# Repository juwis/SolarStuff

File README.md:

# SolarStuff on SolarFlight.info
1. brushless esc with integrated MPPT
 * [Software](https://github.com/juwis/SolarStuff/tree/master/src/autompptbldc)
 * [Hardware](https://github.com/juwis/SolarStuff/tree/master/hardware)
2. Solar Flight optimized Propellers
 * [CAD Data, Prop Data](https://github.com/juwis/SolarStuff/tree/master/props)
3. ...

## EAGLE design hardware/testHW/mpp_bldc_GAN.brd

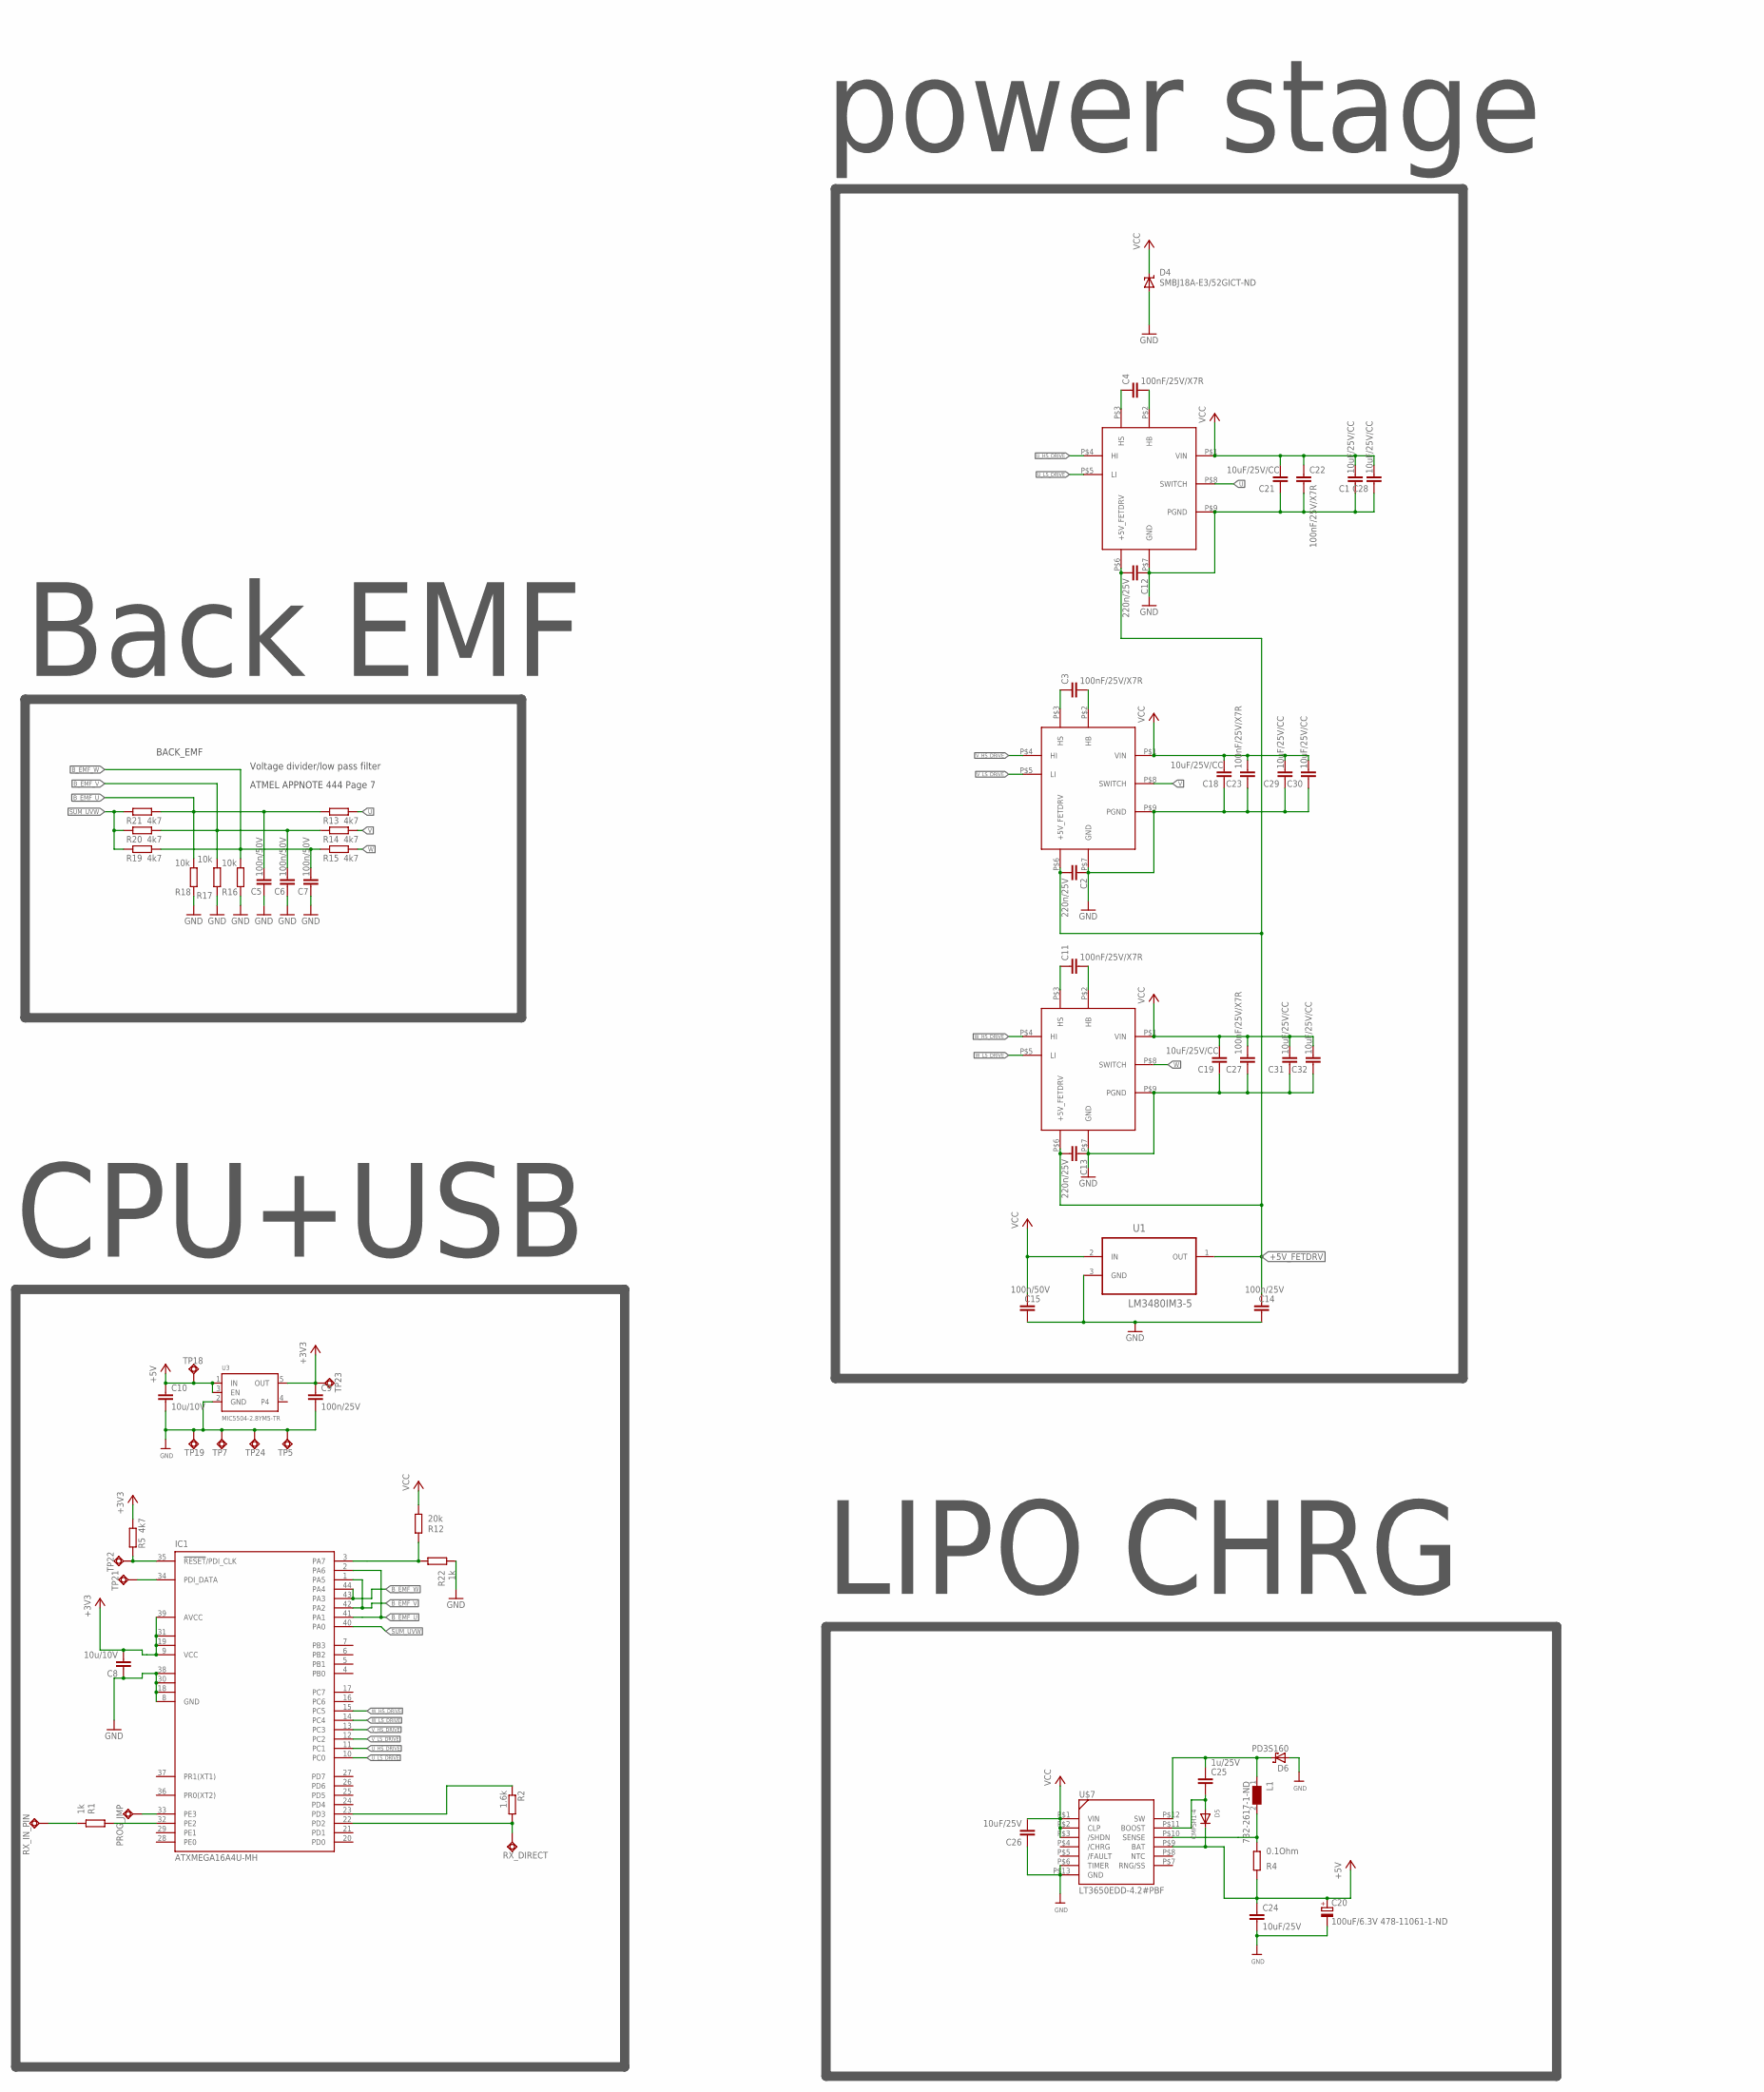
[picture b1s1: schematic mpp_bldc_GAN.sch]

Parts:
C1, C18, C19, C21, C28, C29, C30, C31, C32: 10uF/25V/CC; C1206
C2, C12, C13: 220n/25V; C0402
C3, C4, C11, C22, C23, C27: 100nF/25V/X7R; C0402
C5, C6, C7: 100n/50V; C0402
C8, C10: 10u/10V; C0603K
C9, C14: 100n/25V; C0603
C15: 100n/50V; C0603
C20: 100uF/6.3V 478-11061-1-ND; CT7343
C24, C26: 10uF/25V; C0805
C25: 1u/25V; C0603
D4: SMBJ18A-E3/52GICT-ND; SMBJ
D5: CMPSH1-4; SOT23-R
D6: PD3S160; POWERDI323
IC1: ATXMEGA16A4U-MH; MLF44-TH
L1: 732-2617-1-ND; WE-TPC_2828
PROG_JMP: TPSQTP19SQ; TP19SQ
R1: 1k; R0603
R2: 1.6k; R0402
R4: 0.1Ohm; R0402
R5: 4k7; R0603
R12: 20k; R0402
R13, R14, R15, R19, R20, R21: 4k7; R0402
R16, R17, R18: 10k; R0402
R22: 1k; R0402
RX_DIRECT: TPSQTP11SQ; TP11SQ
RX_IN_PIN: TPSQTP19SQ; TP19SQ
TP5, TP18, TP19: TPSQTP19SQ; TP19SQ
TP7: TPSQTP10R; TP10R
TP21: TPSQTP15R; TP15R
TP22, TP23, TP24: TPSQTP14SQ; TP14SQ
U1: LM3480IM3-5; SOT95P251X112-3N
U3: MIC5504-2.8YM5-TR; SOT23-5
U$1, U$2, U$3: LMG5200
U$7: LT3650EDD-4.2#PBF; 12-WFDFN

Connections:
+3V3: C8.2, C9.1, IC1.9 (VCC), IC1.19 (VCC1), IC1.31 (VCC2), IC1.39 (AVCC), R5.1, TP23.TP, U3.5 (OUT)
+5V: C10.1, C20.+, C24.1, D5.3 (C), R4.2, TP18.TP, U3.1 (IN), U3.3 (EN), U$7.P$9 (BAT)
+5V_FETDRV: C2.2, C12.2, C13.2, C14.2, U1.1 (OUT), U$1.P$6 (+5V_FETDRV), U$2.P$6 (+5V_FETDRV), U$3.P$6 (+5V_FETDRV)
B_EMF_U: C5.1, IC1.2 (PA6), IC1.41 (PA1), R13.2, R18.1, R21.1
B_EMF_V: C6.1, IC1.1 (PA5), IC1.42 (PA2), R14.2, R17.1, R20.1
B_EMF_W: C7.1, IC1.43 (PA3), IC1.44 (PA4), R15.2, R16.1, R19.1
GND: C1.1, C2.1, C5.2, C6.2, C7.2, C8.1, C9.2, C10.2, C12.1, C13.1, C14.1, C15.1, C18.1, C19.1, C20.-, C21.1, C22.2, C23.1, C24.2, C26.1, C27.1, C28.1, C29.1, C30.1, C31.1, C32.1, D4.A, D6.A, IC1.8 (GND), IC1.18 (GND1), IC1.30 (GND2), IC1.38 (GND3), R16.2, R17.2, R18.2, R22.1, TP5.TP, TP7.TP, TP19.TP, TP24.TP, U1.3 (GND), U3.2 (GND), U$1.P$7 (GND), U$1.P$9 (PGND), U$2.P$7 (GND), U$2.P$9 (PGND), U$3.P$7 (GND), U$3.P$9 (PGND), U$7.P$6 (TIMER), U$7.P$13 (GND)
unnamed: IC1.3 (PA7), R12.2, R22.2
unnamed: C3.1, U$2.P$3 (HS)
unnamed: IC1.32 (PE2), R1.2
unnamed: C3.2, U$2.P$2 (HB)
unnamed: C4.1, U$3.P$3 (HS)
unnamed: C4.2, U$3.P$2 (HB)
unnamed: C11.1, U$1.P$3 (HS)
unnamed: C11.2, U$1.P$2 (HB)
unnamed: C25.1, D6.C, L1.1, U$7.P$12 (SW)
unnamed: L1.2, R4.1, U$7.P$10 (SENSE)
unnamed: C25.2, D5.1 (A), U$7.P$11 (BOOST)
PDI_DATA: IC1.34 (PDI_DATA), TP21.TP
PROG_JMP: IC1.33 (PE3), PROG_JMP.TP
RC_SIG_RCV: R1.1, RX_IN_PIN.TP
RST_PDICLK: IC1.35 (!RESET!/PDI_CLK), R5.2, TP22.TP
RX_DIRECT_PD2: IC1.22 (PD2), R2.2, RX_DIRECT.TP
SUM_UVW: IC1.40 (PA0), R19.2, R20.2, R21.2
TX_DIRECT_PD3: IC1.23 (PD3), R2.1
U: R13.1, U$3.P$8 (SWITCH)
U_HS_DRIVE: IC1.11 (PC1), U$3.P$4 (HI)
U_LS_DRIVE: IC1.10 (PC0), U$3.P$5 (LI)
V: R14.1, U$2.P$8 (SWITCH)
VCC: C1.2, C15.2, C18.2, C19.2, C21.2, C22.1, C23.2, C26.2, C27.2, C28.2, C29.2, C30.2, C31.2, C32.2, D4.C, R12.1, U1.2 (IN), U$1.P$1 (VIN), U$2.P$1 (VIN), U$3.P$1 (VIN), U$7.P$1 (VIN), U$7.P$2 (CLP), U$7.P$3 (/SHDN)
V_HS_DRIVE: IC1.13 (PC3), U$2.P$4 (HI)
V_LS_DRIVE: IC1.12 (PC2), U$2.P$5 (LI)
W: R15.1, U$1.P$8 (SWITCH)
W_HS_DRIVE: IC1.15 (PC5), U$1.P$4 (HI)
W_LS_DRIVE: IC1.14 (PC4), U$1.P$5 (LI)

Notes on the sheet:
Voltage divider/low pass filter
ATMEL APPNOTE 444 Page 7
BACK_EMF
power stage
LIPO CHRG
Back EMF
CPU+USB

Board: 6 copper layers, 67 parts (27 on the bottom side), 35 nets, no tracks yet.

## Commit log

2018-07-10 initial commit software
2018-09-16 cleanup
2018-09-16 new version, untested Servo input, running @30degr. timing
2018-09-19 runs :)
2018-09-19 first test for autotune tracker
2018-09-20 initial HW release
2018-09-21 tidy up
2018-09-23 Version 1.0 seems to draw nearer and nearer
2018-09-23 added open hardware symbol :)
2018-10-12 2.8V Supply for uC reduces power draw further Cleanup and some values (ceramics) reduced to buyable ones
2018-10-12 bugfix release, bad coding style leads to bad code...
2018-10-17 cleaning up
2018-10-17 to be checked
2018-10-17 Checked and cleaned up Hardware, repositioned 4 caps
2018-10-23 prop data for solar plane
2018-10-23 cheaper
2018-11-04 Set theme jekyll-theme-time-machine
2018-11-04 Create CNAME
2018-11-04 stronger base, stiffer design
2018-11-14 wip, splitting heirs
2018-11-14 files created for oo based rewrite
2018-11-19 tests
2018-11-20 testing
2018-12-10 Update issue templates
2019-01-16 there we go...
2019-06-04 fixed missing holes, cleanup
